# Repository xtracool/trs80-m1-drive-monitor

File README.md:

# sa400-led-monitor — session workspace

Document: `README.md` · 2026-10-19 · board rev **v0.2.4** (J2 on the component side; not yet fabricated) — boards in hand are **v0.2.3**

Mirror of `C:\Users\ven\Desktop\Projects\_claude\sa400-led-monitor\`. Everything in `sa400_led_monitor/`
is also inside `sa400_led_monitor_v0.2.4.zip`.

## GitHub

Public repo: https://github.com/xtracool/trs80-m1-drive-monitor — the **TRS-80 Model I / Shugart drive monitor**
(a.k.a. TRS-80/Shugart drive monitor project). First commit 2026-10-19 = snapshot of the desktop folder at v0.2.4
(design) / test plan v1.4.

Not in git (see `.gitignore`): the packaged project/handoff zips, `_superseded/`, KiCad `.kicad_prl`. The JLCPCB
order number is masked in the committed copies of the reply notes.

### Working rules for Claude sessions (design and testing)
- **Pull before you start, push when you stop.** The repo is the hand-off point between sessions, not the desktop folder.
- One session edits a given area at a time. Testing session owns `docs/TEST_PLAN.md`, `pdf/build_test_plan.py`,
  `pdf/schematic.tex`, `pdf/fixtures.tex`, `gen/render_populated.py`, `docs/img/`; the design session owns the rest.
- Commit messages: `vX.Y.Z: <what>` for design releases, `testplan vN.M: <what>` for test-plan changes.
- `gen/verify.py` must exit 0 before any design commit that touches `gen/` or `kicad/`.

## Layout

| Path | What it is |
|---|---|
| `jlcpcb_v0.2.4/` | **Next fab set (J2 on top).** Gerber zip, BOM (J2 LCSC blank: consign 1-641737-1 or match C305826 for the vertical header), CPL (all 45 rows Top), render. Do not order until the J2 handedness bench check on the 0.2.3 boards is done (`sa400_led_monitor/docs/ASSEMBLY.md`). |
| `jlcpcb_v0.2.3/` | The set the boards in hand were made from: gerber zip, BOM/CPL, the 2026-10-07 orientation reply to JLCPCB (`jlcpcb_reply_email.txt`, `jlcpcb_orientation_reply.png`, `JLCPCB_REPLY_EMAIL.md`). |
| `jlcpcb_v0.2.2/` | What the current order (SMT0261xxxxxxx (order no. kept off GitHub)) was placed with on 2026-10-05: r2 BOM/CPL, remark, upload guide. Keep for reference. |
| `sa400_led_monitor_design_v0.2.4.pdf` | Full design document, 41 pages, footer on every page; carries the 2026-10-19 design-review corrections (red). |
| `sa400_led_monitor_test_plan_v1.x.pdf` | Bring-up test plan from the testing session (source `sa400_led_monitor/docs/TEST_PLAN.md`, built by `pdf/build_test_plan.py`). |
| `sa400_led_monitor/kicad/` | KiCad 10 project — open `sa400_led_monitor.kicad_pro`. |
| `sa400_led_monitor/gen/` | Python generator (`config.py` is the single source of truth, VERSION = "0.2.4"); `verify.py` release gate; **new** `outputs.py` makes the renders/copper views/STEP/schematic PDF. |
| `sa400_led_monitor/docs/` | THEORY_OF_OPERATION, BOM, MECHANICAL, CABLE, FABRICATION, ASSEMBLY (polarity table), TODO, CHANGELOG, V0.3_PLAN. |
| `sa400_led_monitor/output/` | Gerbers + upload zip, assembly BOM/CPL, DRC/ERC JSON, renders, STEP, schematic PDF. |
| `sa400_led_monitor/pdf/` | LuaLaTeX source (`template.tex`, `build_pdf.py`). |
| `sa400_led_monitor_v0.2.4.zip` | The project as a package. |
| `_superseded/` | v0.2.2 and v0.2.3 packages. |

## What v0.2.4 changed (details in `docs/CHANGELOG.md`)

- J2 moved to the **component side** as a right-angle Commercial Mate-N-Lok header (TE 1-641737-1; vertical
  350211-1 fits the same pads), mating face at the rear edge. JLCPCB's Economic PCBA is single-sided, which is
  why the 0.2.3 boards came back without J2. Pin 1 is now at the H1 end (mirror of the solder-side layout) —
  header handedness is still ASSUMED; bench check before soldering any header (ASSEMBLY.md).
- Power row moved down 2.54 mm for the J2 labels; copper re-routed; DRC/ERC/links clean.
- Merged the testing session's 2026-10-19 doc work (TEST_PLAN.md, design-review corrections in THEORY §3.0/§4.2/§4.3,
  V0.3_PLAN carry-overs F1–F4, render_populated.py, schematic.tex) so both lines of work live in one tree.

## What v0.2.3 changed

- Q1 TO-220 silkscreen redrawn to the real geometry (body over the pins, TAB band toward J2, G/D/S labels).
  JLCPCB's 3D render of v0.2.2 was already correct; only our silk box was on the wrong side.
- Schematic/BOM carry the as-built parts: R1–R8, R21 = 470 Ω; R19 = 2k2; Q1 = IRF4905PBF; LCSC numbers in
  the JLCPCB BOM; sockets as U1A/U2A/U3A with CPL rows. Theory of operation: +5 V budget ≈ 45 mA.
- Copper, mask, drills, outline: identical to v0.2.2 (every layer rendered with gerbv and diffed pixel-wise).

## Rebuild (Windows, KiCad 10.0.x)

```powershell
cd sa400_led_monitor
python gen\verify.py  --kicad-bin "C:/Program Files/KiCad/10.0/bin"   # gate + gerbers + BOM/CPL + upload zip
python gen\outputs.py --kicad-bin "C:/Program Files/KiCad/10.0/bin"   # renders, copper views, STEP, schematic PDF
python pdf\build_pdf.py                                                # design PDF (LuaLaTeX + fontspec/circuitikz)
```

Exit 0 = clean; 1 = a gate failed (message says which); 130 = interrupted.

## Status (2026-10-19)

- 0.2.3 boards received (5, populated except J2); testing in a separate session.
- 0.2.4 designed, verified, not ordered.

## TODO

- [ ] **J2 handedness bench check on a 0.2.3 board** (header in holes, plug on, yellow wire → `+12V` pad); fit the header on whichever side passes. Feed the result into `gen/config.py` (`J2_PIN1_X`, `J2_PIN_DIR`) before ordering 0.2.4.
- [ ] Measure the three ASSUMED dimensions (`J1_TAB_CORNER_GAP`, `J1_KEY_SLOT_W`, `J2_DRILL`) on the 0.2.3 boards.
- [ ] First power-up without the ribbon: D12, D13 lit, 5.0 V on any IC pin 14 — then the test plan.
- [ ] v0.3 (LED-bar modules, 74HCT244 per drive) — `sa400_led_monitor/docs/V0.3_PLAN.md`; J2 stays on the component side.

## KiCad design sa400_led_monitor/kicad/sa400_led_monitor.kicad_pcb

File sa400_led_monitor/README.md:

# sa400_led_monitor v0.2.4

SA400 form-factor board that plugs onto the Shugart 34-pin floppy bus as a fifth "drive" and shows
drive-select (red) and write-gate (green) activity for four drives on eight LEDs. Same card-edge tab and
AMP Mate-N-Lok power header as a Shugart SA400, same power usage (+5 V logic, +12 V present); 5.5 × 5.0 in.
Protected: PTC fuse, P-MOSFET reverse-polarity switch, 5.6 V rail clamp, 470 Ω series resistors between the
bus and the receivers so a board fault cannot damage the host.

## Contents

| Path | What |
|---|---|
| `kicad/` | KiCad 10 project: `.kicad_pro`, `.kicad_sch`, `.kicad_pcb`, `sa400.pretty/`, `sa400.kicad_sym`, lib tables — open the `.kicad_pro` |
| `output/gerbers/`, `output/sa400_led_monitor_v0.2.4_gerbers_JLCPCB.zip` | JLCPCB-ready Gerber X2 + Excellon, plotted by KiCad 10.0.6; the zip is what you upload |
| `output/drc.json`, `output/erc.json` | KiCad 10 DRC (with schematic parity) and ERC reports — both zero |
| `output/sa400_led_monitor_schematic.pdf` | schematic print |
| `output/sa400_led_monitor.step` | 3D STEP |
| `output/render_top.png`, `render_bottom.png` | KiCad 10 raytraced front and back (under solder mask) |
| `output/copper_top.png`, `copper_bottom.png` | F.Cu and B.Cu copper views — use these to check connectivity |
| `output/net_gnd.png`, `net_5v.png`, `net_5v_in.png` | GND, +5V and +5V input nets isolated |
| `output/placement.png`, `j1_vs_photo.png`, `j1_root_holes.png`, `j2_labels.png` | placement and labelling review images |
| `output/BOM.csv`, `output/assembly/` | BOM; JLCPCB BOM (with LCSC numbers) + CPL (incl. socket rows); KiCad position file |
| `pdf/sa400_led_monitor_design_v0.2.4.pdf` | complete design document, built by `pdf/build_pdf.py` from `pdf/template.tex` |
| `docs/THEORY_OF_OPERATION.md` | how the bus and the board work, from first principles; power and fault analysis |
| `docs/MECHANICAL.md` | every dimension with its source; the three left to measure |
| `docs/BOM.md` | bill of materials with sources |
| `docs/FABRICATION.md` | JLCPCB order options and pre-upload checklist |
| `docs/ASSEMBLY.md` | KiCad 10 pre-flight steps, assembler comparison |
| `docs/CABLE.md`, `output/cable.png` | six-connector TRS-80 Model I drive cable |
| `docs/TEST_PLAN.md` | bring-up test plan: unpowered → bench supply + bus-simulator jig → on the EI, with record sheets; §0.7 = 2026-10-19 design-review findings; appendices A board wireframe + legend, B schematic, C as-built parts list |
| `pdf/schematic.tex`, `docs/img/schematic.pdf` | one-page circuitikz schematic, as built, drawn from the `design.py` netlist (the KiCad print is `output/sa400_led_monitor_schematic.pdf`) |
| `docs/V0.3_PLAN.md` | next board: LED-bar modules + 74HCT244 per drive, decided, not started |
| `docs/TODO.md`, `docs/CHANGELOG.md` | |
| `gen/` | Python generator — the design source of truth |

## Regenerating

    python3 gen/build.py                                   # placement -> routing -> DRC -> kicad/, BOM, assembly files
    <kicad>/bin/python3 gen/postprocess.py kicad/sa400_led_monitor.kicad_pcb   # KiCad flips any back-side part (none since 0.2.4), fills zones, writes F8 metadata
    python3 gen/verify.py --kicad-bin "C:/Program Files/KiCad/10.0/bin"        # release gate: all of the above + DRC/ERC/links/plots
    gen/check.ps1                                          # Windows: same steps via PowerShell
    python3 gen/outputs.py --kicad-bin "C:/Program Files/KiCad/10.0/bin"        # review outputs: raytraced renders, copper views, schematic PDF, STEP, placement/net images
    python3 gen/render_populated.py          # output/board_populated.png/.pdf (wireframe, as-built values)
    python3 pdf/build_test_plan.py           # pdf/sa400_led_monitor_test_plan_v1.3.pdf from docs/TEST_PLAN.md (needs pandoc; builds pdf/schematic.tex too)
    python3 pdf/build_pdf.py                 # design PDF (LuaLaTeX) from pdf/template.tex + config VERSION + CHANGELOG.md + TODO.md

Exit codes: 0 ok, 1 build/DRC failure, 130 Ctrl-C.

All dimensions live in `gen/config.py` with their source in the comment; anything marked ASSUMED is listed
in `docs/MECHANICAL.md` with the config name to change.

## Status

v0.2.x: 5 populated boards on order at JLCPCB (re-ordered 2026-10-05 with the fab files only; engineering
query about Q1 orientation answered 2026-10-07 — their render was right, our 0.2.2 silkscreen was not).
0.2.3 = the 0.2.2 copper with the corrected Q1 silkscreen, the as-built values (470 Ω LED resistors, 2k2,
IRF4905PBF) and the LCSC-matched JLCPCB BOM. **0.2.4 (2026-10-19, not yet fabricated)** moves J2 to the
component side as a right-angle header so a single-sided PCBA order populates every part; the J2
handedness bench check in `docs/ASSEMBLY.md` must be done on the 0.2.3 boards before 0.2.4 is ordered.
KiCad 10 DRC (with schematic parity) and ERC both zero.
Three physical measurements remain to confirm on the first boards (`docs/TODO.md`).

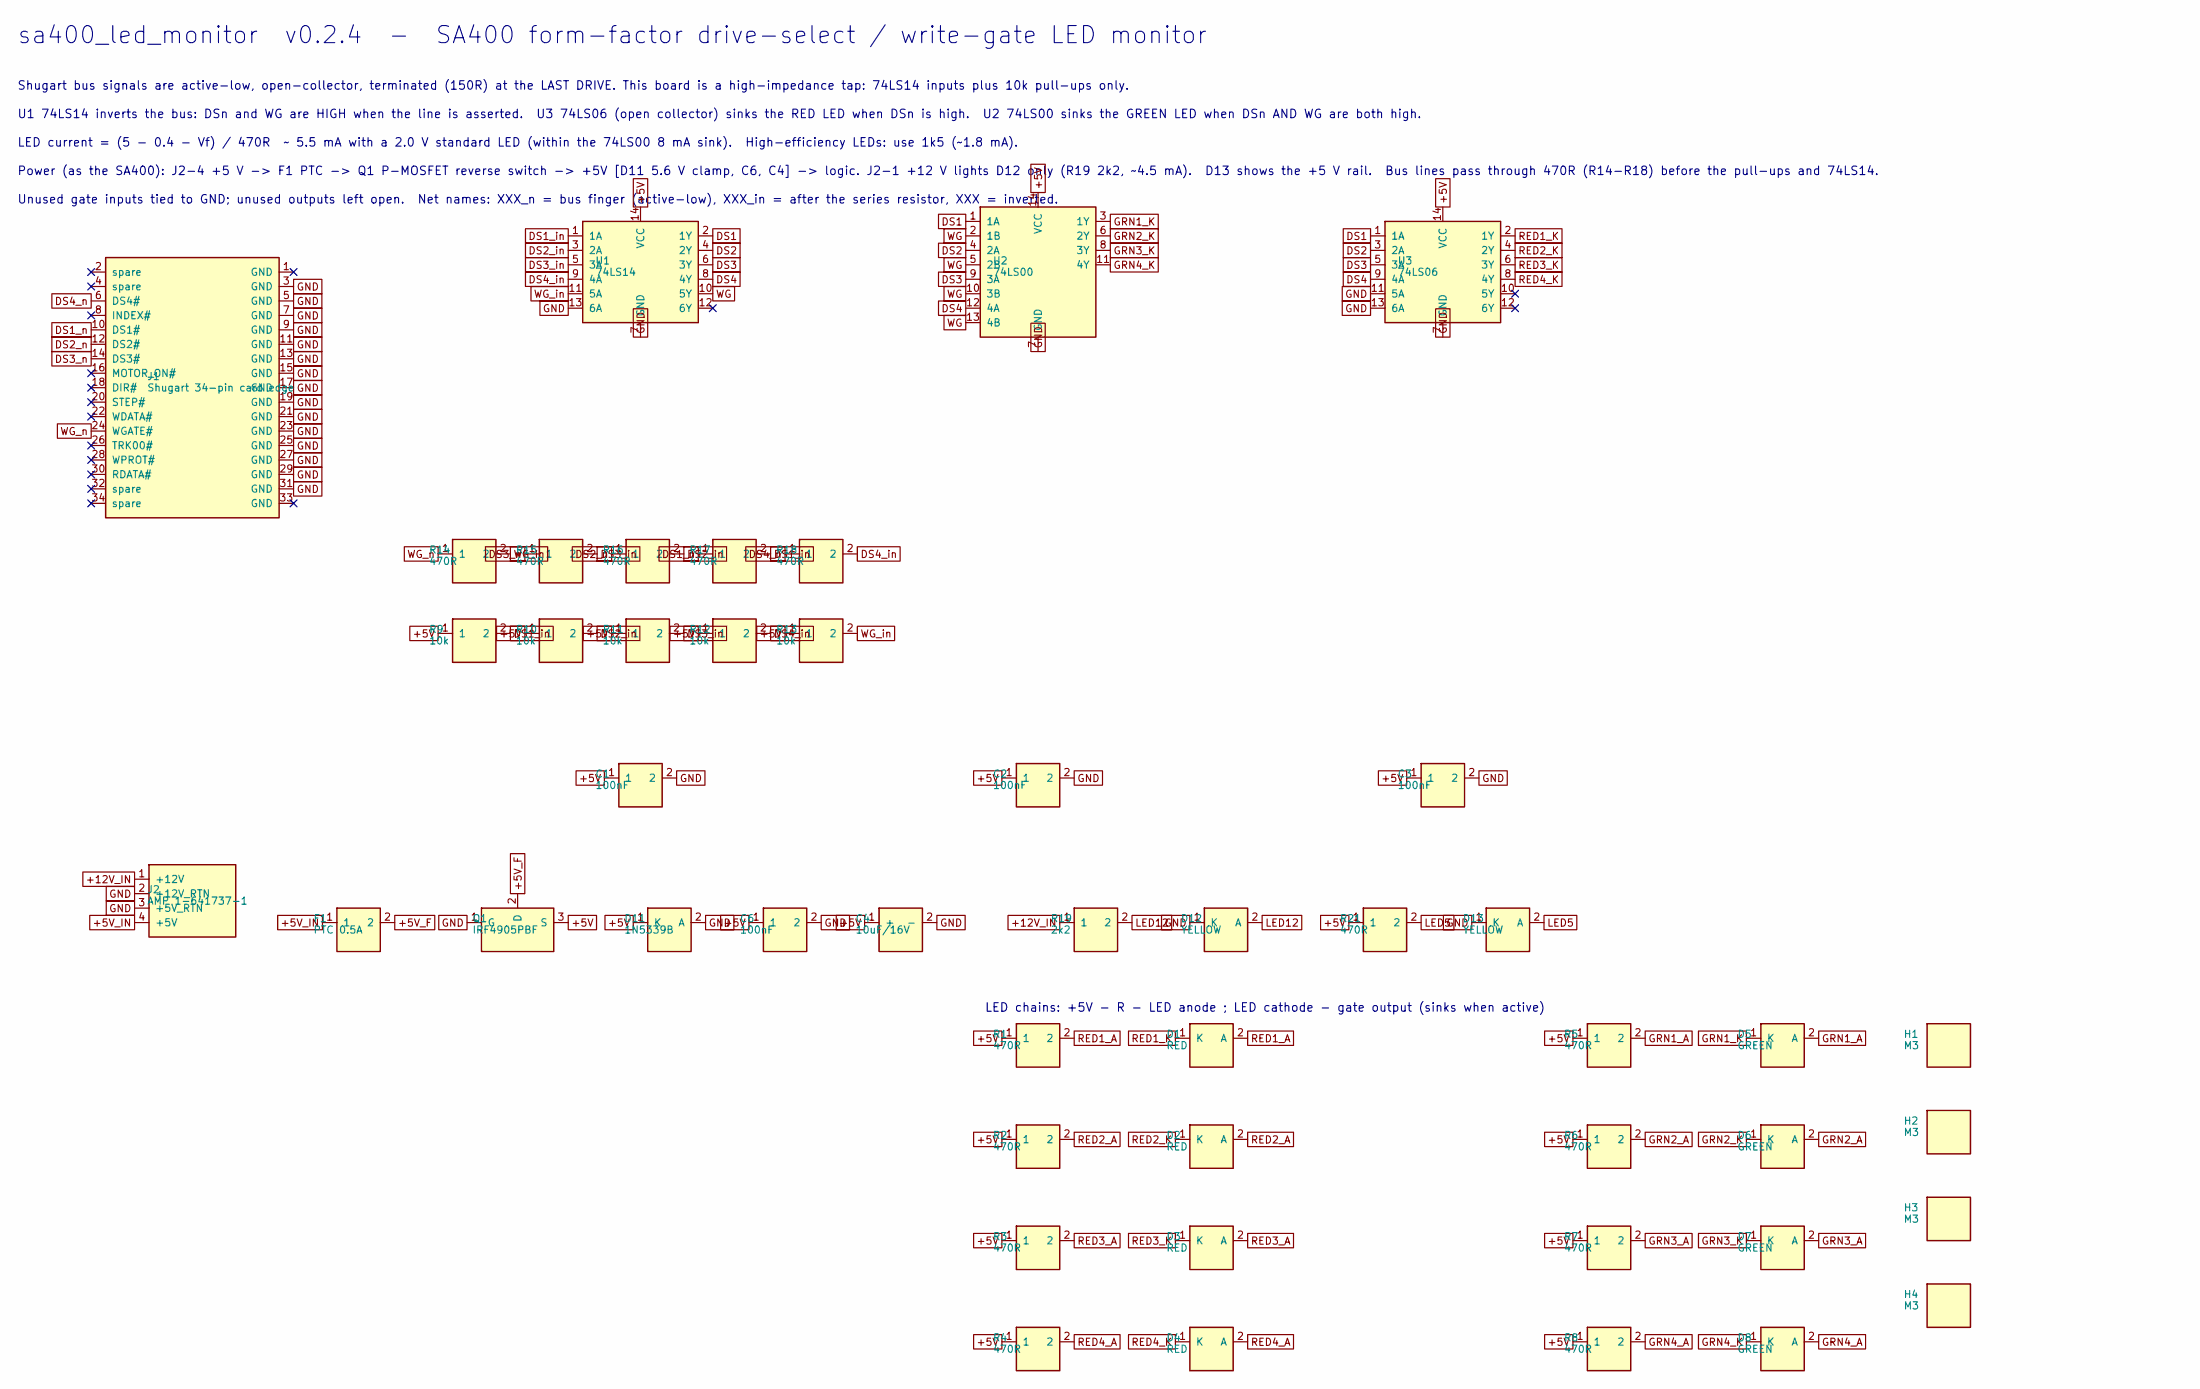
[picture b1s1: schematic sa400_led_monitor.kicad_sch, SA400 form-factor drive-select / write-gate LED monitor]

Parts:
C1, C2, C3, C6: 100nF; C_Disc_D5.0mm_P2.50mm
C4: 10uF/16V; CP_Radial_D5.0mm_P2.50mm
D1, D2, D3, D4: RED; LED_D5.0mm
D5, D6, D7, D8: GREEN; LED_D5.0mm
D11: 1N5339B; D_DO-15_P10.16mm_Vertical
D12, D13: YELLOW; LED_D5.0mm
F1: PTC 0.5A; Fuse_Radial_P5.08mm
H1, H2, H3, H4: M3; MountingHole_3.2mm_M3
J1: Shugart 34-pin card edge; CardEdge_34_SA400
J2: AMP 1-641737-1; MateNLok_4_RA
Q1: IRF4905PBF; TO-220-3_Vertical
R1, R2, R3, R4, R5, R6, R7, R8, R14, R15, R16, R17, R18, R21: 470R; R_Axial_DIN0207_P7.62mm_Vertical
R9, R10, R11, R12, R13: 10k; R_Axial_DIN0207_P7.62mm_Vertical
R19: 2k2; R_Axial_DIN0207_P7.62mm_Vertical
U1: 74LS14; DIP-14_W7.62mm
U2: 74LS00; DIP-14_W7.62mm
U3: 74LS06; DIP-14_W7.62mm

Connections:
+5V: C1.1, C2.1, C3.1, C4.1 (+), C6.1, D11.1 (K), Q1.3 (S), R1.1, R2.1, R3.1, R4.1, R5.1, R6.1, R7.1, R8.1, R9.1, R10.1, R11.1, R12.1, R13.1, R21.1, U1.14 (VCC), U2.14 (VCC), U3.14 (VCC)
+5V_F: F1.2, Q1.2 (D)
+5V_IN: F1.1, J2.4 (+5V)
+12V_IN: J2.1 (+12V), R19.1
DS1: U1.2 (1Y), U2.1 (1A), U3.1 (1A)
DS1_in: R9.2, R17.2, U1.1 (1A)
DS1_n: J1.10 (DS1#), R17.1
DS2: U1.4 (2Y), U2.4 (2A), U3.3 (2A)
DS2_in: R10.2, R16.2, U1.3 (2A)
DS2_n: J1.12 (DS2#), R16.1
DS3: U1.6 (3Y), U2.9 (3A), U3.5 (3A)
DS3_in: R11.2, R15.2, U1.5 (3A)
DS3_n: J1.14 (DS3#), R15.1
DS4: U1.8 (4Y), U2.12 (4A), U3.9 (4A)
DS4_in: R12.2, R18.2, U1.9 (4A)
DS4_n: J1.6 (DS4#), R18.1
GND: C1.2, C2.2, C3.2, C4.2 (-), C6.2, D11.2 (A), D12.1 (K), D13.1 (K), J1.3 (GND), J1.5 (GND), J1.7 (GND), J1.9 (GND), J1.11 (GND), J1.13 (GND), J1.15 (GND), J1.17 (GND), J1.19 (GND), J1.21 (GND), J1.23 (GND), J1.25 (GND), J1.27 (GND), J1.29 (GND), J1.31 (GND), J2.2 (+12V_RTN), J2.3 (+5V_RTN), Q1.1 (G), U1.7 (GND), U1.13 (6A), U2.7 (GND), U3.7 (GND), U3.11 (5A), U3.13 (6A)
GRN1_A: D5.2 (A), R5.2
GRN1_K: D5.1 (K), U2.3 (1Y)
GRN2_A: D6.2 (A), R6.2
GRN2_K: D6.1 (K), U2.6 (2Y)
GRN3_A: D7.2 (A), R7.2
GRN3_K: D7.1 (K), U2.8 (3Y)
GRN4_A: D8.2 (A), R8.2
GRN4_K: D8.1 (K), U2.11 (4Y)
LED5: D13.2 (A), R21.2
LED12: D12.2 (A), R19.2
RED1_A: D1.2 (A), R1.2
RED1_K: D1.1 (K), U3.2 (1Y)
RED2_A: D2.2 (A), R2.2
RED2_K: D2.1 (K), U3.4 (2Y)
RED3_A: D3.2 (A), R3.2
RED3_K: D3.1 (K), U3.6 (3Y)
RED4_A: D4.2 (A), R4.2
RED4_K: D4.1 (K), U3.8 (4Y)
WG: U1.10 (5Y), U2.2 (1B), U2.5 (2B), U2.10 (3B), U2.13 (4B)
WG_in: R13.2, R14.2, U1.11 (5A)
WG_n: J1.24 (WGATE#), R14.1

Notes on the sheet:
sa400_led_monitor v0.2.4 - SA400 form-factor drive-select / write-gate LED monitor
Shugart bus signals are active-low, open-collector, terminated (150R) at the LAST DRIVE. This board is a high-impedance tap: 74LS14 inputs plus 10k pull-ups only.
U1 74LS14 inverts the bus: DSn and WG are HIGH when the line is asserted. U3 74LS06 (open collector) sinks the RED LED when DSn is high. U2 74LS00 sinks the GREEN LED when DSn AND WG are both high.
LED current = (5 - 0.4 - Vf) / 470R ~ 5.5 mA with a 2.0 V standard LED (within the 74LS00 8 mA sink). High-efficiency LEDs: use 1k5 (~1.8 mA).
Power (as the SA400): J2-4 +5 V -> F1 PTC -> Q1 P-MOSFET reverse switch -> +5V [D11 5.6 V clamp, C6, C4] -> logic. J2-1 +12 V lights D12 only (R19 2k2, ~4.5 mA). D13 shows the +5 V rail. Bus lines pass through 470R (R14-R18) before the pull-ups and 74LS14.
Unused gate inputs tied to GND; unused outputs left open. Net names: XXX_n = bus finger (active-low), XXX_in = after the series resistor, XXX = inverted.
LED chains: +5V - R - LED anode ; LED cathode - gate output (sinks when active)

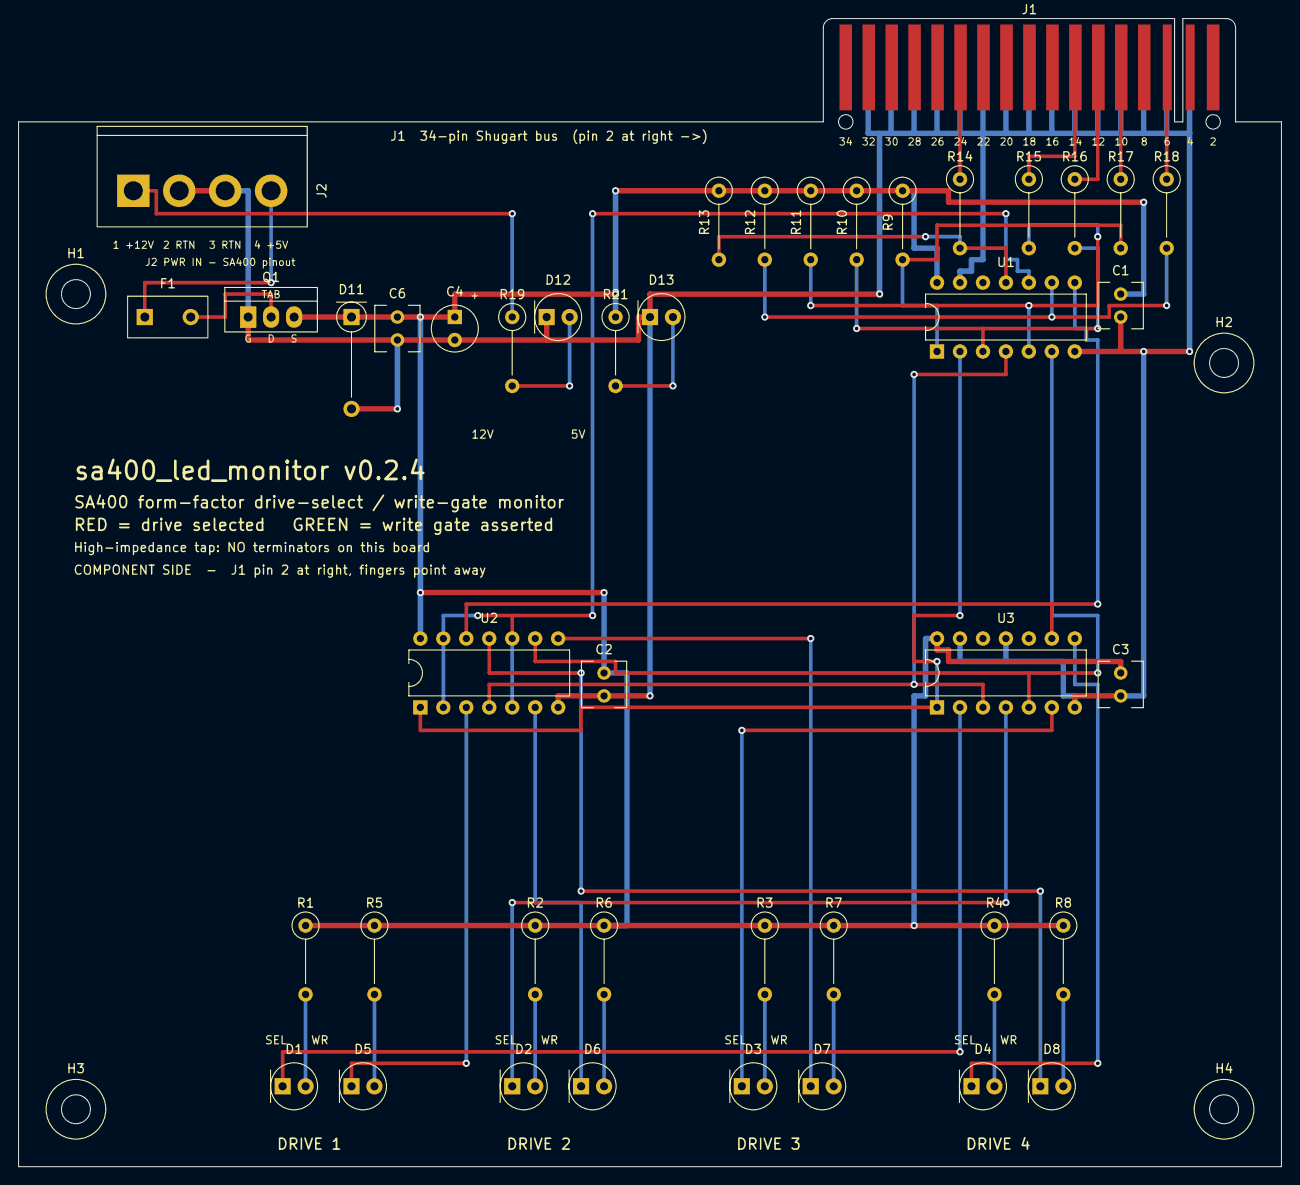
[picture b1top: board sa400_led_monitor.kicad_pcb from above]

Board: 2 copper layers, 139.7 x 127.0 mm, 47 parts (0 on the bottom side), 38 nets.

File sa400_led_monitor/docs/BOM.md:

# Bill of Materials — sa400_led_monitor v0.2.4

Document: `BOM.md` · 2026-10-19 · All parts through-hole. Quantities per board.
Machine-readable copies: `output/BOM.csv`, `output/assembly/BOM_jlcpcb.csv` (with the LCSC numbers below).
LCSC numbers are the parts JLCPCB matched and we accepted for the first assembled batch.

## Active

| Qty | Ref | Part | Package | Example part / source |
|---|---|---|---|---|
| 1 | U1 | 74LS14 hex Schmitt-trigger inverter | DIP-14 | TI SN74LS14N (LCSC C73064) — https://www.ti.com/product/SN74LS14 · https://www.mouser.com/c/?q=SN74LS14N |
| 1 | U2 | 74LS00 quad 2-input NAND | DIP-14 | TI SN74LS00N (LCSC C181629) — https://www.ti.com/product/SN74LS00 · https://www.mouser.com/c/?q=SN74LS00N |
| 1 | U3 | 74LS06 hex inverter, open-collector | DIP-14 | TI SN74LS06N (LCSC C22384767) — https://www.ti.com/product/SN74LS06 · https://www.mouser.com/c/?q=SN74LS06N |
| 3 | U1A–U3A | DIP-14 IC socket | DIP-14 | any dual-wipe 14-pin socket (LCSC C190815) |

## Protection and indicators

| Qty | Ref | Part | Package | Example part / source |
|---|---|---|---|---|
| 1 | F1 | PTC resettable fuse, 0.5 A hold / 1 A trip, ≥ 16 V | radial 5.08 mm | A72-050 (LCSC C135425) or Littelfuse RUEF050 — https://www.mouser.com/c/?q=RUEF050 |
| 1 | Q1 | P-channel MOSFET, pins **G-D-S** | TO-220 vertical, tab toward the J2 edge | IRF4905PBF (LCSC C2564) — https://www.mouser.com/c/?q=IRF4905PBF · logic-level alternative onsemi NDP6020P — https://www.mouser.com/c/?q=NDP6020P |
| 1 | D11 | Zener 5.6 V 5 W, +5 V rail clamp | DO-15 vertical | 1N5339B (LCSC C5444832) — https://www.mouser.com/c/?q=1N5339B |
| 2 | D12, D13 | Yellow 5 mm LED, standard brightness ("12V" / "5V" present) | 5 mm | Kingbright WP483YDT (LCSC C6001325) — https://www.mouser.com/c/?q=WP483YDT |

Zener band (cathode) and LED cathodes go in the **square** pads. Q1: gate is pin 1 (square pad), metal tab toward the J2 edge — the silk shows the body, tab line and G/D/S.

## Drive-state LEDs

| Qty | Ref | Part | Package | Example part / source |
|---|---|---|---|---|
| 4 | D1–D4 | Red 5 mm LED, standard brightness, Vf ≈ 1.9 V | 5 mm | Kingbright L-53ID (LCSC C598429) — https://www.mouser.com/c/?q=L-53ID · high-efficiency WP7113LID also fits (then R1–R4 = 1.5 kΩ) |
| 4 | D5–D8 | Green 5 mm LED, standard brightness, Vf ≈ 2.1 V | 5 mm | Kingbright WP7113GD (LCSC C7117617) — https://www.mouser.com/c/?q=WP7113GD · high-efficiency WP7113LGD also fits (then R5–R8 = 1.5 kΩ) |

Cathode = shorter lead / flat side of the rim, into the **square** pad (pin 1).

## Passives

| Qty | Ref | Value | Package | Notes |
|---|---|---|---|---|
| 8 | R1–R8 | 470 Ω ±5 % ¼ W | axial, vertical 7.62 mm | LED series, ≈ 5.5 mA (YAGEO MFR-25JT-52-470R, LCSC C176518). Use 1.5 kΩ with high-efficiency LEDs (≈ 1.8 mA). |
| 5 | R9–R13 | 10 kΩ ±5 % ¼ W | axial, vertical 7.62 mm | Bus input pull-ups (YAGEO MFR-25JT-52-10K, LCSC C176451) |
| 5 | R14–R18 | 470 Ω ±5 % ¼ W | axial, vertical 7.62 mm | Bus series / fault-limiting (between finger and receiver) (LCSC C176518) |
| 1 | R19 | 2.2 kΩ ¼ W | axial, vertical 7.62 mm | +12 V indicator series, ≈ 4.5 mA (YAGEO MFR-25FTE52-2K2 1 %, LCSC C172997) |
| 1 | R21 | 470 Ω ±5 % ¼ W | axial, vertical 7.62 mm | +5 V indicator series, ≈ 6 mA (LCSC C176518) |
| 4 | C1, C2, C3, C6 | 100 nF 50 V ceramic | disc, 2.5 mm pitch | IC decoupling (C1–C3), rail entry (C6) (LCSC C45664, 2.0 mm pitch fits the pads) |
| 1 | C4 | 10 µF 16 V electrolytic | radial 5 mm dia, 2.5 mm pitch | Bulk on +5 V. **+ lead in the square pad.** (LCSC C53330112) |

## Connectors and hardware

| Qty | Ref | Part | Source |
|---|---|---|---|
| — | J1 | 34-contact card edge, part of the PCB (gold fingers, bevel — fab option) | — |
| 1 | J2 | TE Commercial Mate-N-Lok 4-position **right-angle** PCB header **1-641737-1**, component side (SA400 pinout: 1 +12 V indicator, 2/3 RTN, 4 +5 V logic) | https://www.te.com/en/product-1-641737-1.html · https://www.mouser.com/c/?q=1-641737-1 · https://www.digikey.com/en/products/result?keywords=1-641737-1 — if unavailable, the **vertical** 350211-1 fits the same pads (LCSC C305826, https://www.te.com/en/product-350211-1.html) |
| 4 | H1–H4 | M3 × 6 mm standoff + M3 screw, or #4-40 | any |

## Mating parts (not on the board)

| Item | Part | Source |
|---|---|---|
| Bus cable connector | 3M 3463-0001, 34-way card-edge IDC | datasheet https://multimedia.3m.com/mws/media/22013O/3m-tm-100-in-card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 · https://www.mouser.com/c/?q=3463-0001 |
| Key plug for the pin 4/6 slot | 3M 3439-2 | https://www.mouser.com/c/?q=3439-2 |
| Power plug | AMP 1-480424-0 housing + 60619-1 pins (standard drive power connector) | https://www.te.com/en/product-1-480424-0.html |

## PCB

| Item | Spec |
|---|---|
| Size | 139.70 × 127.00 mm (5.5 × 5.0 in), 45.59 mm tab protruding from the recessed rear edge |
| Layers / copper | 2, 1 oz |
| Thickness | 1.6 mm (3M spec 1.37–1.78) |
| Finish | ENIG, **gold fingers + bevel** selected in the JLCPCB order options |
| Fab | JLCPCB, gerbers in `output/gerbers/` |

## Cost estimate (single board, 2026 distributor pricing)

| Group | Approx |
|---|---|
| ICs + sockets | $4 |
| Protection + indicators (PTC, MOSFET, Zener, 2 LEDs) | $3 |
| Drive LEDs | $2 |
| Passives | $1 |
| J2 | $1 |
| Standoffs | $1 |
| PCB (JLCPCB, 5 pcs, gold-finger option) | $25–35 for the batch |

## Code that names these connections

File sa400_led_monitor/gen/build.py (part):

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        xs = [c[1] for c in cells]; ys = [c[2] for c in cells]
        return (max(xs) - min(xs)) + (max(ys) - min(ys))
    signal.sort(key=span)
    bus = ["WG_n", "DS3_n", "DS2_n", "DS1_n", "DS4_n"]          # constrained: single exit from the fingers
    order = bus + [n for n in signal if n not in bus] + ["+5V", "GND"]
    for n in order:
        w = C.POWER_W if n in ("GND", "+5V") else C.TRACE_W
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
